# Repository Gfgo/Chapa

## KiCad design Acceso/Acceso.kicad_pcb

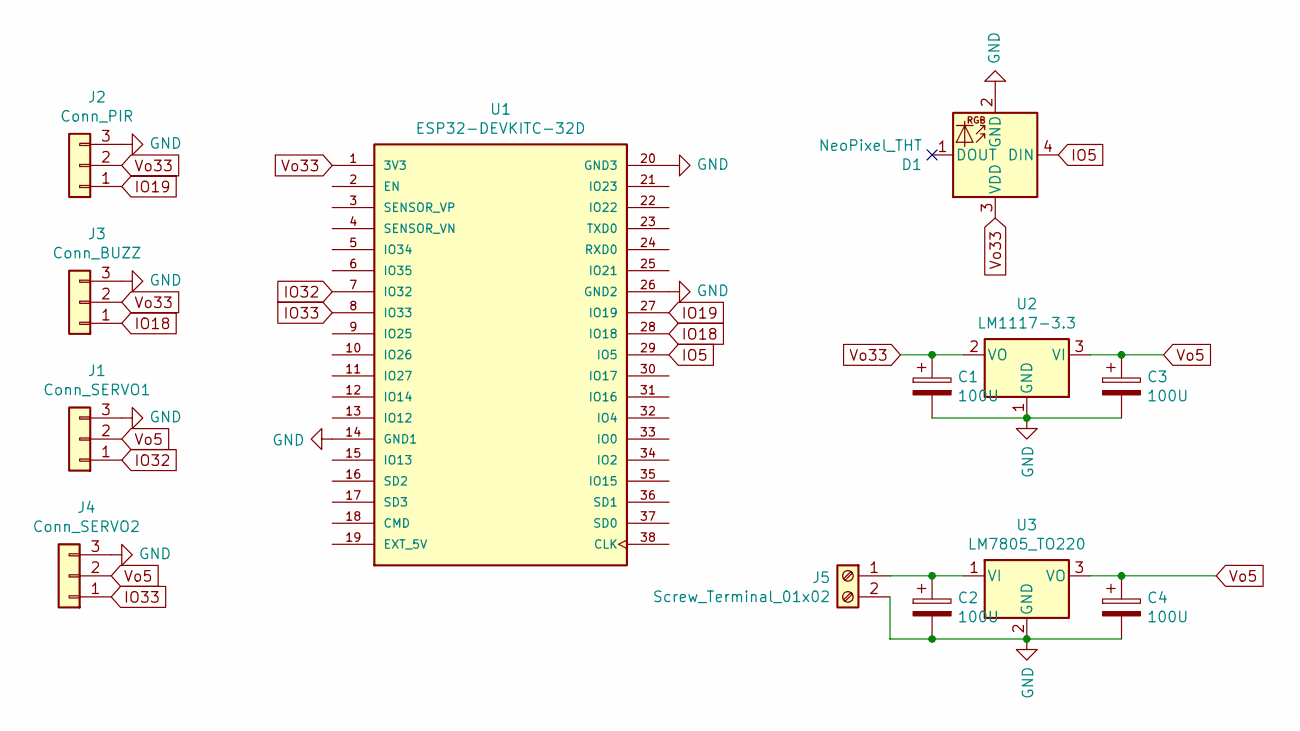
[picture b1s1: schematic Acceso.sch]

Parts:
C1, C2, C3, C4: 100U; CP_Radial_D5.0mm_P2.50mm
D1: NeoPixel_THT; PinHeader_1x04_P2.54mm_Vertical
J1: Conn_SERVO1; PinHeader_1x03_P2.54mm_Vertical
J2: Conn_PIR; PinHeader_1x03_P2.54mm_Vertical
J3: Conn_BUZZ; PinHeader_1x03_P2.54mm_Vertical
J4: Conn_SERVO2; PinHeader_1x03_P2.54mm_Vertical
J5: Screw_Terminal_01x02; TerminalBlock_Phoenix_MKDS-1,5-2-5.08_1x02_P5.08mm_Horizont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
U1: ESP32-DEVKITC-32D; Esp32wroverD; PARTREV 4
U2: LM1117-3.3; TO-220-3_Vertical
U3: LM7805_TO220; TO-220-3_Vertical

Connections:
GND: C1.2, C2.2, C3.2, C4.2, D1.2 (GND), J1.3, J2.3, J3.3, J4.3, J5.2, U1.14 (GND1), U1.20 (GND3), U1.26 (GND2), U2.1 (GND), U3.2 (GND)
IO5: D1.4 (DIN), U1.29 (IO5)
IO18: J3.1, U1.28 (IO18)
IO19: J2.1, U1.27 (IO19)
IO32: J1.1, U1.7 (IO32)
IO33: J4.1, U1.8 (IO33)
unnamed: C2.1, J5.1, U3.1 (VI)
Vo5: C3.1, C4.1, J1.2, J4.2, U2.3 (VI), U3.3 (VO)
Vo33: C1.1, D1.3 (VDD), J2.2, J3.2, U1.1 (3V3), U2.2 (VO)

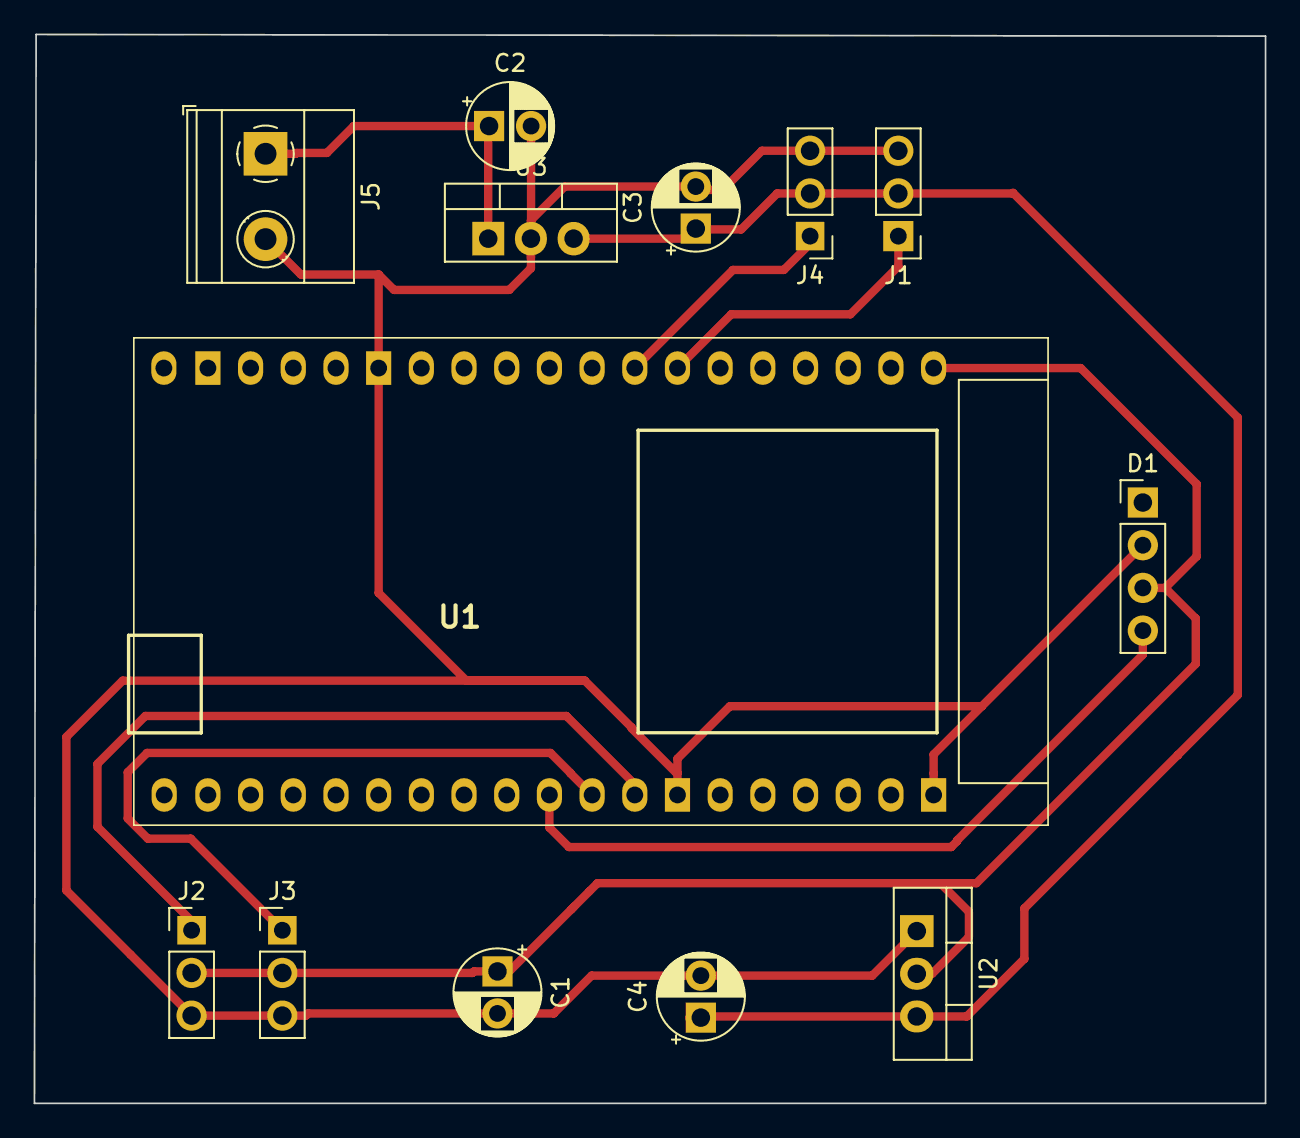
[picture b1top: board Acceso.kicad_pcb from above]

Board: 2 copper layers, 73.2 x 63.6 mm, 13 parts (0 on the bottom side), 9 nets.

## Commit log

2021-10-28 Create Chapa.ino
    Primer programa 28/10 lectura de datos y envió por BLE
2021-10-28 Inicio de programación envió y selección por BLE.
2021-10-29 Controlservoy BLE
2021-11-03 Inicio
2021-11-03 Correción de seriaEvent
2021-11-03 Correcion de errores
2021-11-04 Cambio de motores
2021-11-05 Inclusion de buser led y sharp no funca
2021-11-08 Implementacion de luces
2021-11-08 Luces y motores ok
2021-11-09 luz y sharp no funcionan bien
2021-11-10 cambio sharp por pir luces no funcionan.
2021-11-11 Todo ok funcionando, todo alimentado desde el esp.
2022-12-07 Todo listo.
2023-06-20 PCB e info
2024-05-22 actualización 22/05
    actualización 22/05
